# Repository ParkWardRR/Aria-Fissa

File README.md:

# Aria Fissa Project
This project hopes to simplify monitoring CO2 levels using Home-Assistant or the more compatible MQTT protocol. 
Aria Fissa uses the easily procurable CO2 sensor (MH-Z19) and the NodeMCU v3.

## Ingredients

 - MH-Z19 sensor - [Link](https://esphome.io/components/sensor/mhz19.html)
 -  Microcontroller - NodeMCU v3 - [Link](https://docs.zerynth.com/latest/official/board.zerynth.nodemcu3/docs/index.html) 
	- The Aria Fissa PCB might be compatible with other ESP8266  board. Verify the pin count and the RX/TX pin locations 
- Host - You'll need a [MQTT broker](https://en.wikipedia.org/wiki/MQTT#MQTT_broker) or [Home-Assistant](https://www.home-assistant.io/getting-started/) host 
- Computer to configure the board and your host 
- Soldering iron, solder, flux, and other hobbiest tools/consumables

### Optional 
There are few variations of the MH-Z19 - The Aria Fissa board attempts compatablity with most of the available versions. 

There are two options to mount the MH-Z19 to the PCB: 
 -  MH-Z19 by using 2.54mm pitch breakaway male pin headers ( 9 total pins needed) 
 -  There are through-hole solder pads located near the middle of the board for mounting a JST connector. This might provide some users additional mounting options. 
	 - Search for the following: `JST 1.25MM 7 Pin Female Double Connector with Wires 150MM 1007 28 AWG`
	 - *Not all MH-Z19 sensors have a JST mount*

 For mounting the NodeMCU board either solder it directly to the PCB or use `2.54mm Pitch 0.1 1x15 15 Pin 15p Female Dupont Header`
 
 Here is a fully functioning board: 

## Next Steps/Tutorials
Configure the NodeMCU board for your environment

 - MQTT Tutorial
 - [Home-Assistant (using ESPHome)](Aria-Fissa/ESPHome-config/)

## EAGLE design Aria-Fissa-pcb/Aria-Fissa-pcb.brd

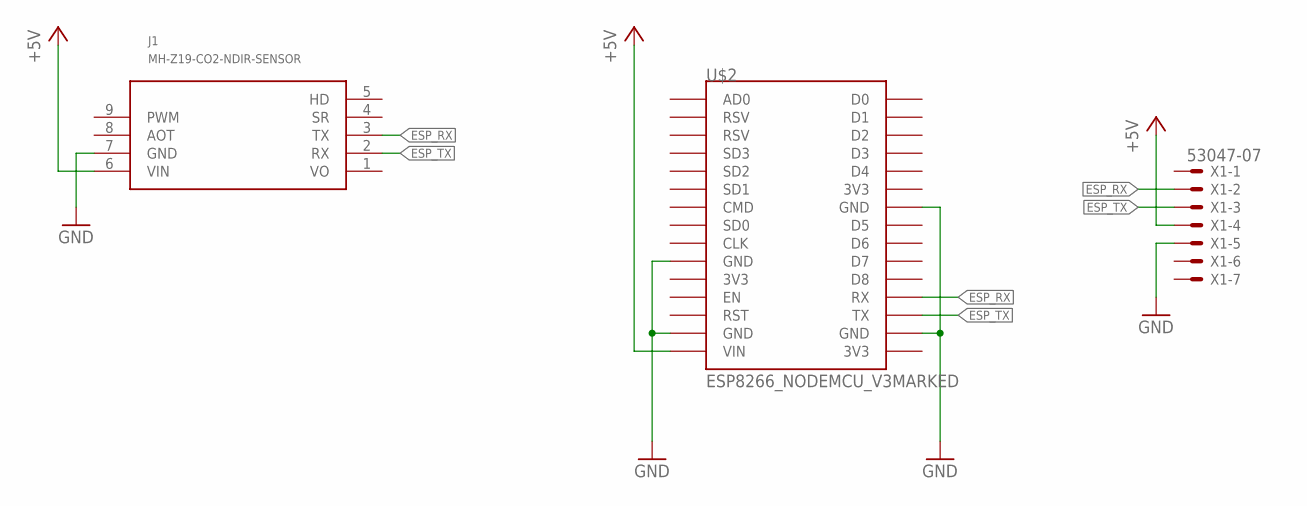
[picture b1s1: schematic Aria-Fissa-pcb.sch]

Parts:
J1: MH-Z19-CO2-NDIR-SENSOR; MH-Z19
U$2: ESP8266_NODEMCU_V3MARKED; ESP8266_NODEMCU_V3_SMALL
X1: 53047-07

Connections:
+5V: J1.6 (VIN), U$2.VIN, X1.4
ESP_RX: J1.3 (TX), U$2.RX, X1.2
ESP_TX: J1.2 (RX), U$2.TX, X1.3
GND: J1.7 (GND), U$2.GND@0 (GND), U$2.GND@1 (GND), U$2.GND@2 (GND), U$2.GND@3 (GND), X1.5
VO: J1.1 (VO)

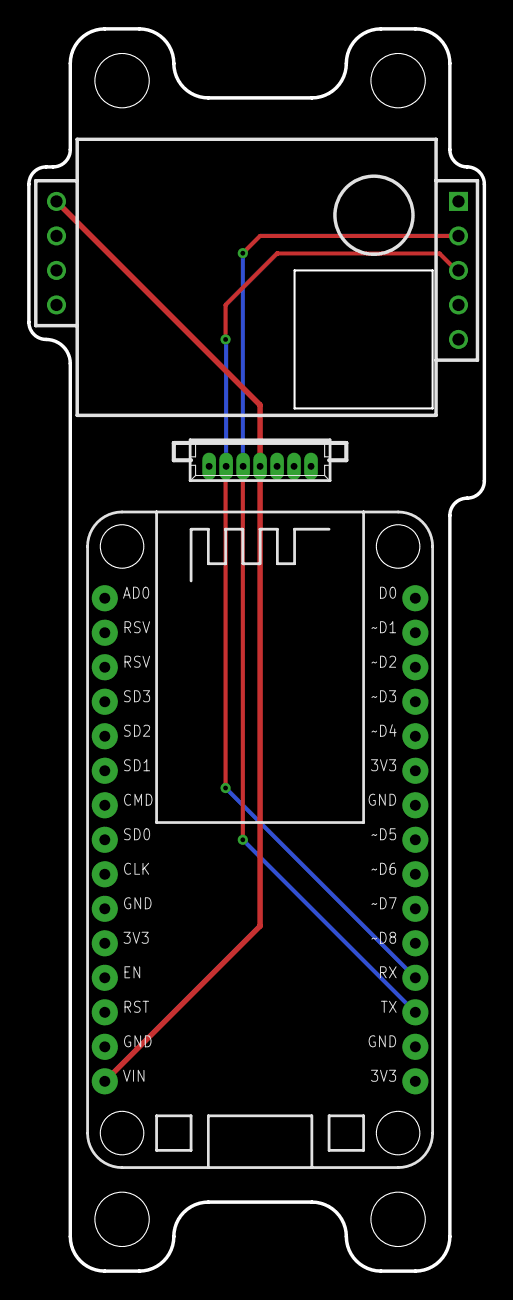
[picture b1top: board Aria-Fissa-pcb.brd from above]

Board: 2 copper layers, 33.5 x 91.4 mm, 3 parts (1 on the bottom side), 4 nets.

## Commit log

2020-06-12 Uploaded v2 of the PCB files
2020-06-12 ESPHome commit
2020-06-12 ESPHome - Yaml
2020-06-12 ESPHome
2020-06-17 Tutorials Folder Upload
2020-06-17 .ds_store remove
2020-06-17 MQTT tutorial
